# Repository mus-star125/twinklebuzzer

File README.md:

# ⭐ Twinkl Buzzer

A small PCB project that plays **Twinkle Twinkle Little Star** using a buzzer!

I wanted to make something simple, fun, and interactive while learning more about electronics, PCB design, and how different components work together.

The idea is pretty straightforward: press the button, and the buzzer plays the melody of Twinkle Twinkle Little Star. There's also an LED as a visual indicator.

##  Features

-  A buzzer that plays Twinkle Twinkle Little Star
-  
-  A push button to activate the melody
-  
-  An LED indicator
-  
-  A compact custom-designed PCB
-  
-  A resistor to limit current through the LED

## Components & BOM

| Component | Quantity | Purpose |
|---|---:|---|
| PCB | 1 | Holds all the components and connections |
| Buzzer | 1 | Plays Twinkle Twinkle Little Star |
| LED (Red) | 1 | Visual indicator |
| Resistor 10 | 1 | Limits current through the LED |
| Push button | 1 | Activates the melody |
| Microcontroller esp32 ardiono| 1 | Controls the buzzer and LED |

## How It Works
The project uses a buzzer to produce the different notes of Twinkle Twinkle Little Star

Each note has a different frequency, which is controlled through the program. The notes are played one after another to create the melody

When the button is pressed, the program triggers the song, and the LED acts as a visual indicator
## Programming

The melody is created by programming individual musical notes and their durations

The code controls:
- The frequency of each note
- How long each note plays
- The pauses between notes
- The button input
- The LED indicator

##  PCB Design

The PCB was designed in KiCad. I arranged the components and routed the connections to bring the circuit together into one board.

##  What I Learned

Through this project, I got to explore:
- PCB design and component placement.
- How buzzers produce different tones.
- How resistors work in a circuit.
- How push buttons interact with electronic circuits.
- Connecting hardware with code.

This is a small project, but it's another step in learning how to turn an idea into something physical!

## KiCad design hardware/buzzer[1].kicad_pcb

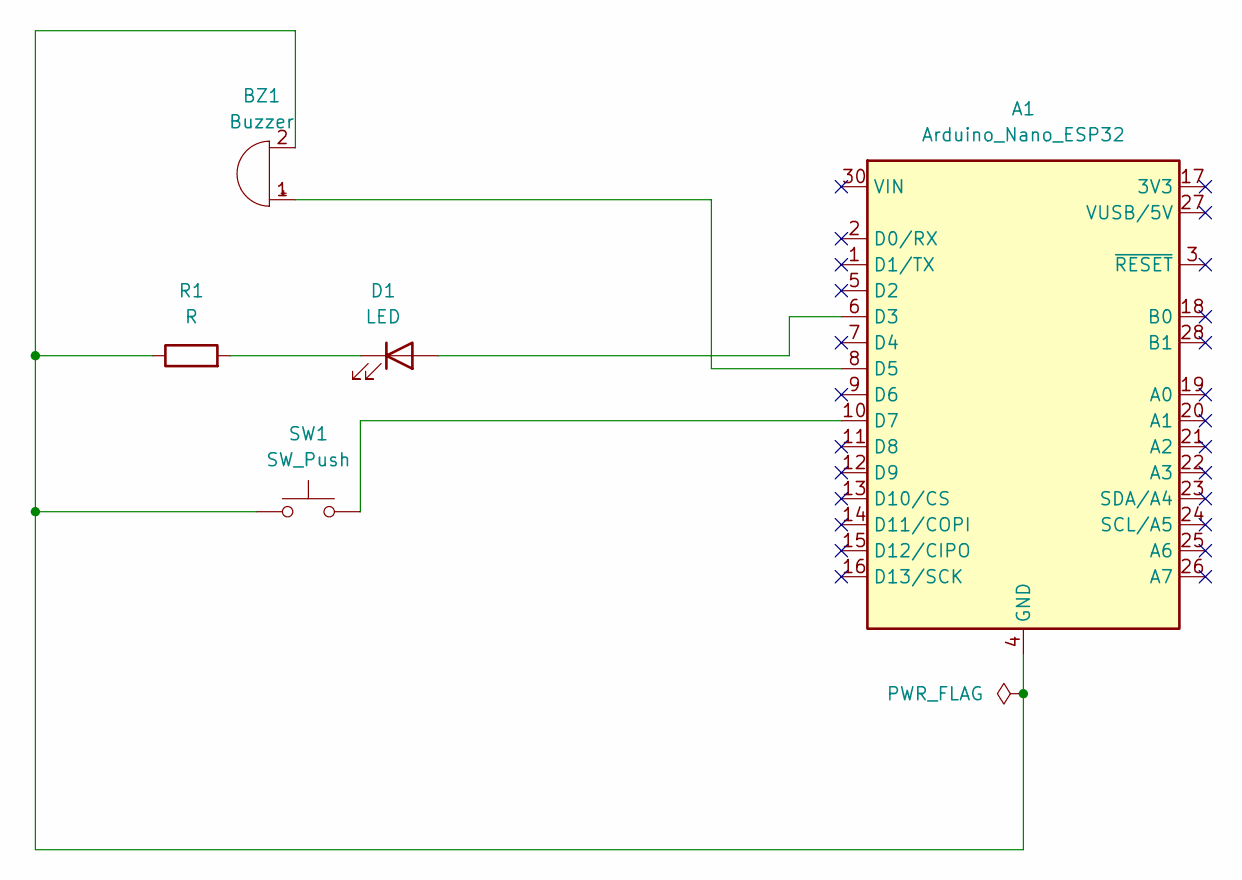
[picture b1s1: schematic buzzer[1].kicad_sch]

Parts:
A1: Arduino_Nano_ESP32; Arduino_Nano
BZ1: Buzzer; Buzzer_D14mm_H7mm_P10mm
D1: LED; LED_D5.0mm
R1: R; R_Axial_DIN0207_L6.3mm_D2.5mm_P7.62mm_Horizontal
SW1: SW_Push; SW_PUSH_6mm

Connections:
unnamed: A1.6 (D3), D1.2 (A)
unnamed: A1.8 (D5), BZ1.1 (+)
unnamed: A1.10 (D7), SW1.2
unnamed: A1.4 (GND), A1.29 (GND), BZ1.2 (-), R1.1, SW1.1
unnamed: D1.1 (K), R1.2

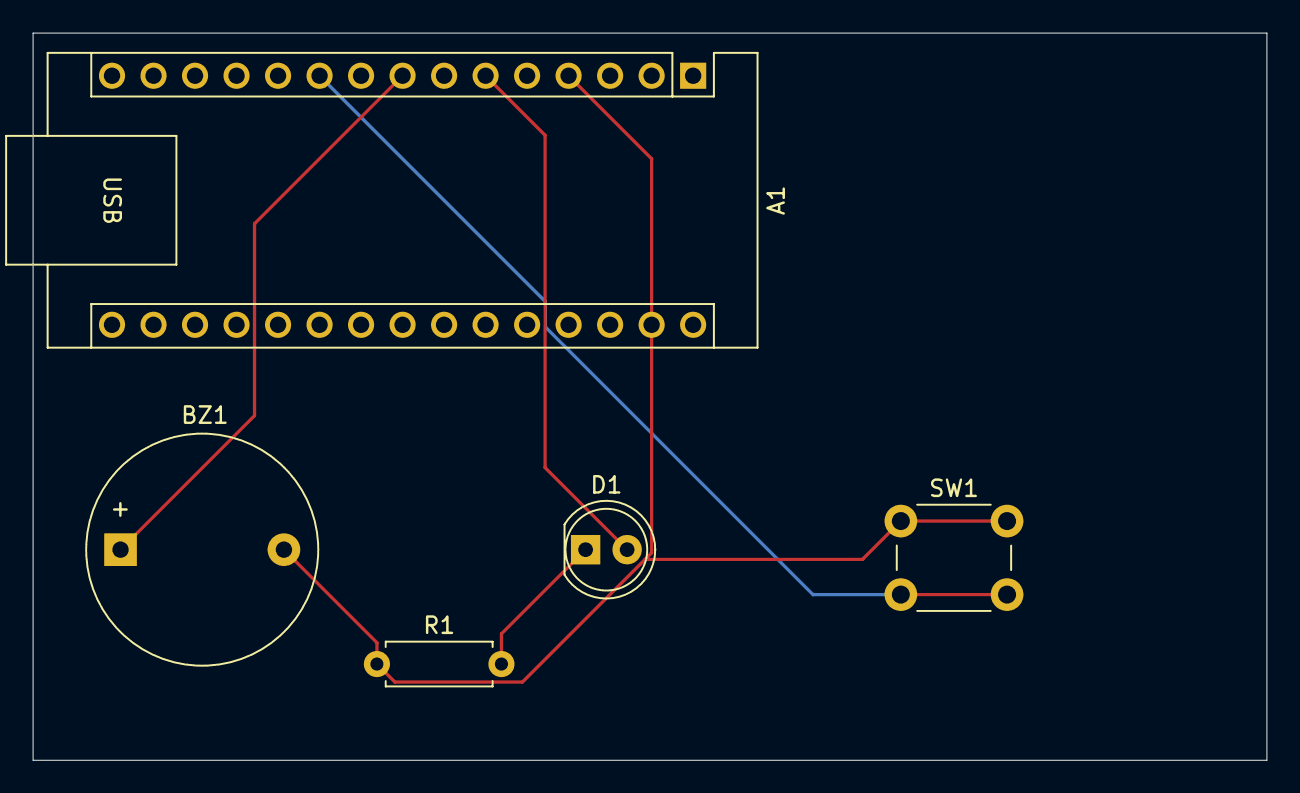
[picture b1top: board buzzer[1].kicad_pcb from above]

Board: 2 copper layers, 75.5 x 44.5 mm, 5 parts (0 on the bottom side), 5 nets.
